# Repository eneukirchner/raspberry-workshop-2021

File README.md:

# Program examples and utilities for Raspberry Pi 

## Programming 
(_directories: Python, Qt, c, curses-games_)

For compiling / running the code examples, the following software packages are needed - most of them
are part of _Raspberry Pi OS bullseye_ distribution and can be installed with ```sudo apt install <package name>```.

- Qt Widget:
```qtbase5-dev qtchooser qt5-qmake qtbase5-dev-tools qtcreator```

- QML: 
```qml-module-qtquick-* qtquickcontrols2* qtdeclarative5-dev```

- PyQt:
```python3-pyqt5*  pyqt5-dev-tools python3-paho-mqtt```

- curses:
```ncurses-dev```

There is one important exception: _wiringPi_, which was used for all examples for controlling GPIO so far, is no longer
available in the latest Raspberry OS release. As a replacement, I have decided to use _lgpio_, because of mainly two
strong points: (1) It uses the new _gpiochip_ kernel interface and (2) it does not require ```sudo``` for
running the compiled programs. Unfortunately, it is not (yet) part of the distribution. You have to build and install
it from source <http://abyz.me.uk/lg/download.html>.

## BULME Hat hardware
(_directory: hardware_)

Board Dimensions: 65 x 56 mm

(TOP) *Name-Layer and Value Layer*  -> *Silkscreen*

*Important Notice:* Unless otherwise specified, Eagle files
use layer 21 and 25 for silkscreen

## Shell scripts etc. for Raspberry Pi setup
(_directory: tools_)

- find-raspi.php
Run this in a webserver to find ip address of Raspberry in subnet (if zeroconf is unavailable)

- klabu
Ping all hostnames.local from list in subnet

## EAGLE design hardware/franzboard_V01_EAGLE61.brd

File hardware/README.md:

# "Franzboard" Hardware

Boardgröße: 65 x 56 mm

Bitte Oberseite (TOP) *Name-Layer und Value Layer* als *Bestückungsdruck*

*Wichtiger Hinweis:* Wenn nicht anders angegeben, werden bei Eagle-Dateien
standardmäßig Layer 21 und 25 für den Bestückungsdruck ausgegeben.

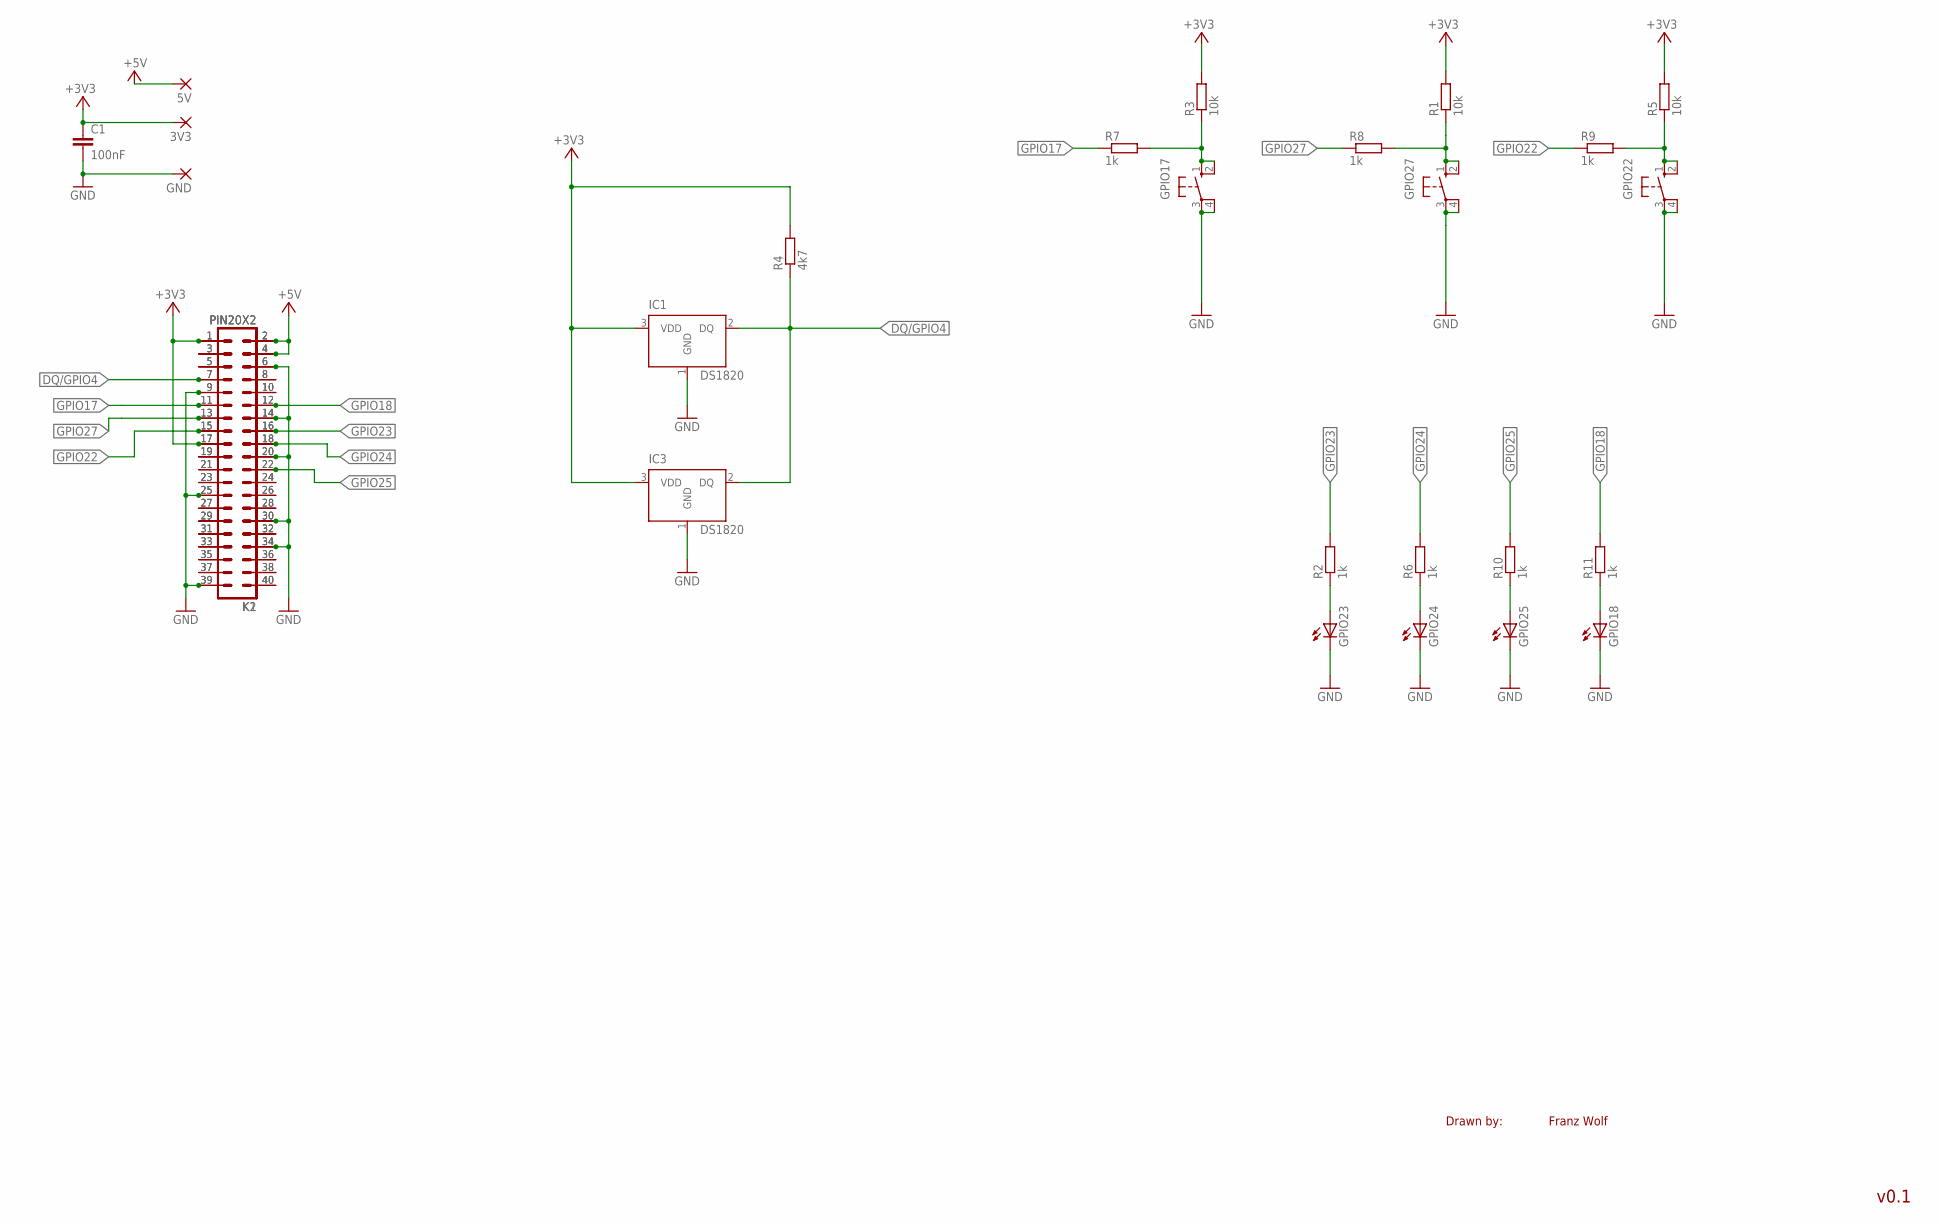
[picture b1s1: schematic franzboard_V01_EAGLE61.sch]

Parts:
3V3, 5V: 1,6/0,8
C1: 100nF; C1206
GND: 1,6/0,8
GPIO17, GPIO22, GPIO27: 10-XX; B3F-10XX; MPN B3F-1000
GPIO18, GPIO23, GPIO24, GPIO25: LEDSMT1206; 1206
IC1, IC3: DS1820; TO-92
K1, K2: PIN20X2; PIN_20X2
R1, R3, R5: 10k; R1206
R2, R6, R7, R8, R9, R10, R11: 1k; R1206
R4: 4k7; R1206

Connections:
+3V3: 3V3.1, C1.1, IC1.3 (VDD), IC3.3 (VDD), K1.1, K1.17, K2.1, K2.17, R1.2, R3.2, R4.2, R5.2
+5V: 5V.1, K1.2, K1.4, K2.2, K2.4
DQ/GPIO4: IC1.2 (DQ), IC3.2 (DQ), K1.7, K2.7, R4.1
GND: C1.2, GND.1, GPIO17.3, GPIO17.4 (P1), GPIO18.C, GPIO22.3, GPIO22.4 (P1), GPIO23.C, GPIO24.C, GPIO25.C, GPIO27.3, GPIO27.4 (P1), IC1.1 (GND), IC3.1 (GND), K1.6, K1.9, K1.14, K1.20, K1.25, K1.30, K1.34, K1.39, K2.6, K2.9, K2.14, K2.20, K2.25, K2.30, K2.34, K2.39
GPIO17: K1.11, K2.11, R7.1
GPIO18: K1.12, K2.12, R11.2
GPIO22: K1.15, K2.15, R9.1
GPIO23: K1.16, K2.16, R2.2
GPIO24: K1.18, K2.18, R6.2
GPIO25: K1.22, K2.22, R10.2
GPIO27: K1.13, K2.13, R8.1
unnamed: K1.3, K2.3
unnamed: K1.5, K2.5
unnamed: GPIO23.A, R2.1
unnamed: GPIO17.1 (S), GPIO17.2 (S1), R3.1, R7.2
unnamed: GPIO27.1 (S), GPIO27.2 (S1), R1.1, R8.2
unnamed: GPIO22.1 (S), GPIO22.2 (S1), R5.1, R9.2
unnamed: GPIO24.A, R6.1
unnamed: GPIO25.A, R10.1
unnamed: GPIO18.A, R11.1
unnamed: K1.19, K2.19
unnamed: K1.21, K2.21
unnamed: K1.23, K2.23
unnamed: K1.24, K2.24
unnamed: K1.26, K2.26
unnamed: K1.27, K2.27
unnamed: K1.29, K2.29
unnamed: K1.28, K2.28
unnamed: K1.31, K2.31
unnamed: K1.33, K2.33
unnamed: K1.32, K2.32
unnamed: K1.36, K2.36
unnamed: K1.38, K2.38
unnamed: K1.40, K2.40
unnamed: K1.35, K2.35
unnamed: K1.37, K2.37
RXD: K1.10, K2.10
TXD: K1.8, K2.8

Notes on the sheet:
Drawn by:
Franz Wolf
v0.1

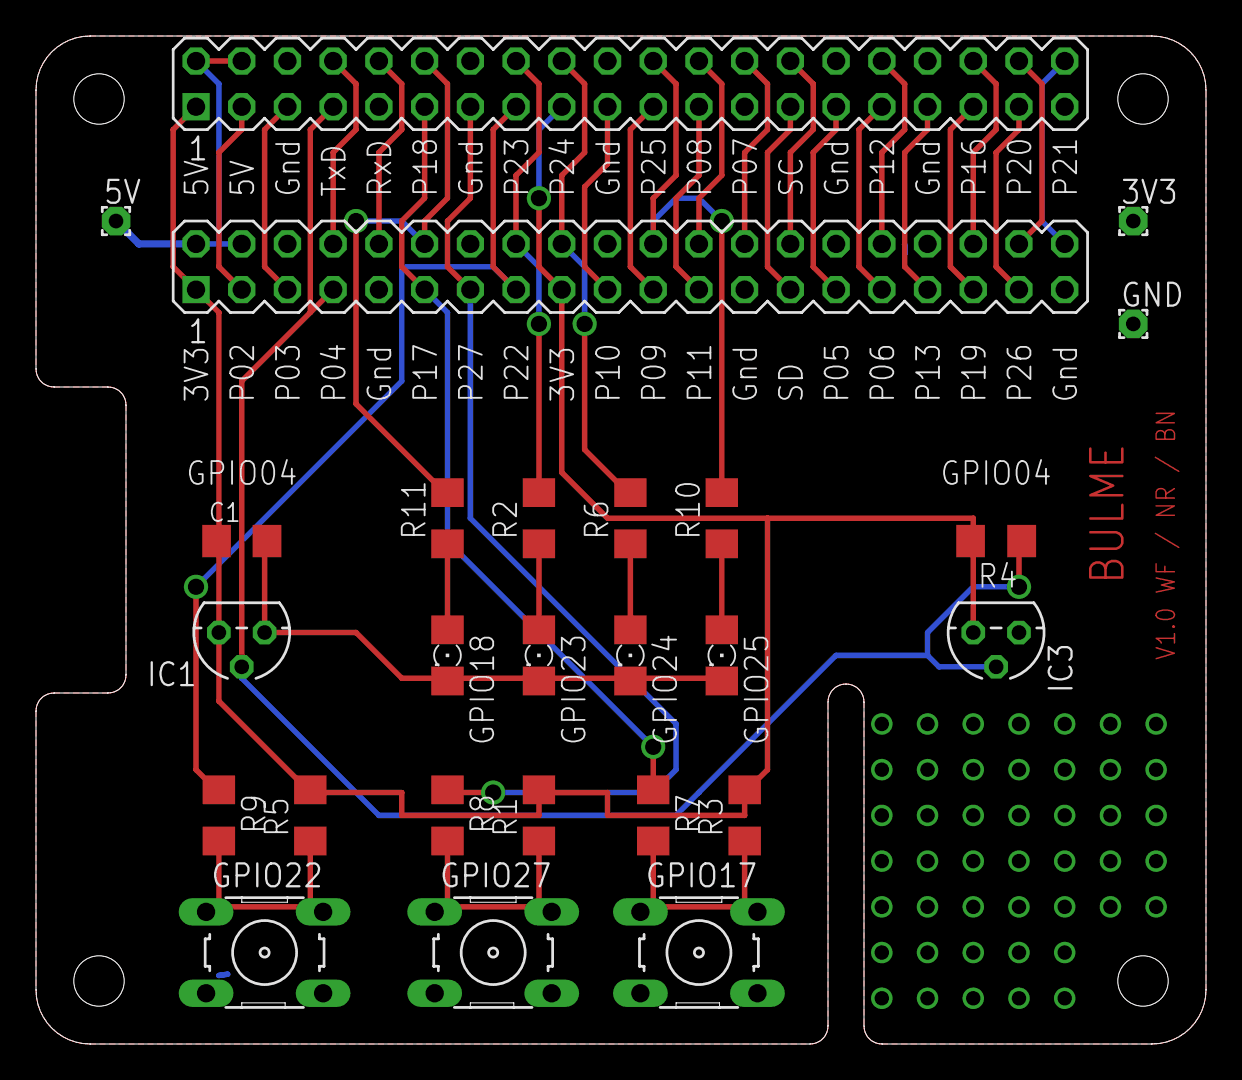
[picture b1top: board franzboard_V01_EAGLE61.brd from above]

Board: 2 copper layers, 65.0 x 56.0 mm, 26 parts (0 on the bottom side), 38 nets.

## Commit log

2021-11-01 hardware description
2021-11-01 stash removed
2021-11-08 Samuel added
2021-11-08 Samuel deleted
2021-11-08 Samuel/blink.c deleted
2021-11-09 migrated: wiringPi -> lgpio
2021-11-09 README.md updated
2021-11-09 modify README.md
2021-11-11 stash and moc* deleted
2021-11-11 race binary deleted
